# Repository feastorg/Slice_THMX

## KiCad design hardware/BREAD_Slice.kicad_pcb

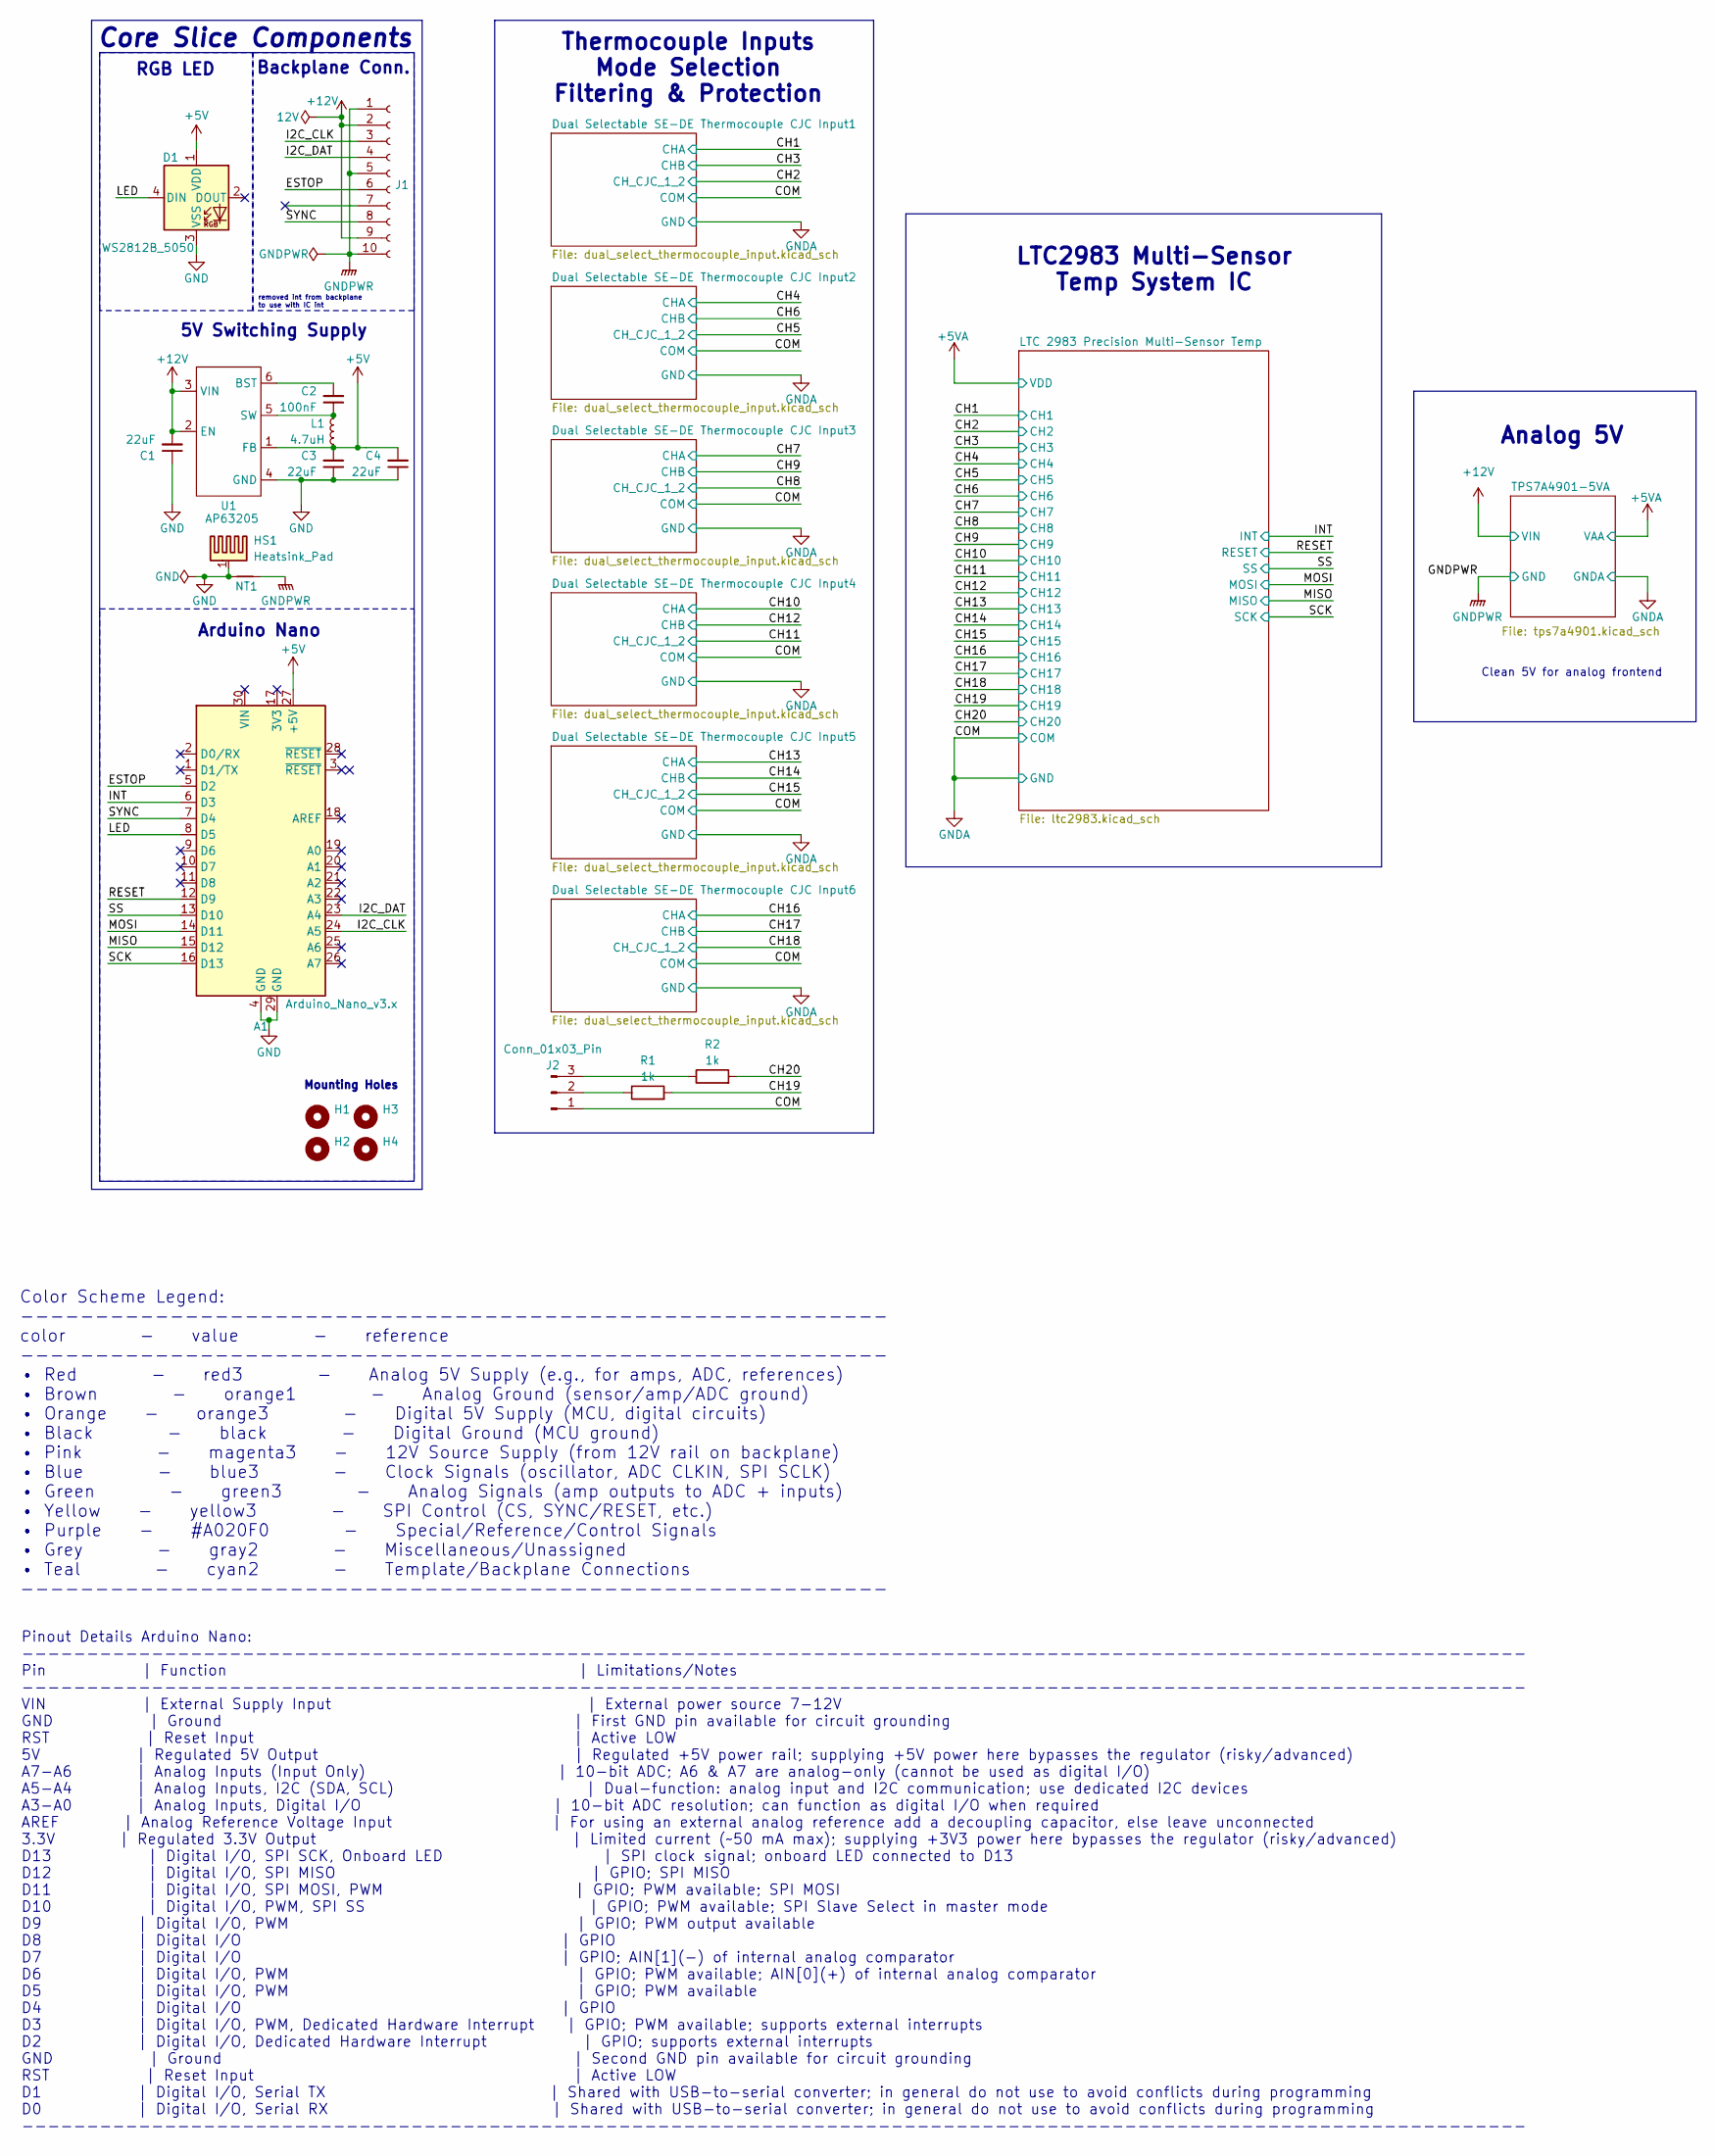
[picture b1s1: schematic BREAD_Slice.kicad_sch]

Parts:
A1: Arduino_Nano_v3.x; Arduino_Nano
C1, C3, C4: 22uF; C_1206_3216Metric
C2: 100nF; C_1206_3216Metric
D1: WS2812B_5050; WS2812-5050-4PIN
H1, H2, H3, H4: MountingHole; MountingHole_5mm
HS1: Heatsink_Pad; Thermal_Pad
J1: Conn_01x10_Female; PinSocket_1x10_P2.54mm_Horizontal
J2: Conn_01x03_Pin; PinHeader_1x03_P2.54mm_Vertical
L1: 4.7uH; L_1210_3225Metric
NT1: NetTie_2; NetTie-2_SMD_Pad2.0mm
R1, R2: 1k; R_0603_1608Metric_Pad0.98x0.95mm_HandSolder
U1: AP63205; TSOT-23-6

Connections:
+5V: A1.27 (+5V), C3.2, C4.2, D1.1 (VDD), L1.2, U1.1 (FB)
+12V: C1.2, J1.2, J1.9, U1.2 (EN), U1.3 (VIN); also elsewhere on the board
/CH19: R1.2; also elsewhere on the board
/CH20: R2.2; also elsewhere on the board
/ESTOP: A1.5 (D2), J1.6
/I2C_CLK: A1.24 (A5), J1.3
/I2C_DAT: A1.23 (A4), J1.4
/INT: A1.6 (D3); also elsewhere on the board
/LED: A1.8 (D5), D1.4 (DIN)
/MISO: A1.15 (D12); also elsewhere on the board
/MOSI: A1.14 (D11); also elsewhere on the board
/RESET: A1.12 (D9); also elsewhere on the board
/SCK: A1.16 (D13); also elsewhere on the board
/SS: A1.13 (D10); also elsewhere on the board
/SYNC: A1.7 (D4), J1.8
GND: A1.4 (GND), A1.29 (GND), C1.1, C3.1, C4.1, D1.3 (VSS), HS1.1, NT1.1, U1.4 (GND)
GNDA: J2.1; also elsewhere on the board
GNDPWR: J1.1, J1.5, J1.10, NT1.2; also elsewhere on the board
unnamed: J2.2, R1.1
unnamed: J2.3, R2.1
unnamed: C2.2, U1.6 (BST)
unnamed: C2.1, L1.1, U1.5 (SW)

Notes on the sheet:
Clean 5V for analog frontend
removed int from backplane to use with IC int
5V Switching Supply
Analog 5V
Thermocouple Inputs Mode Selection Filtering & Protection
Pinout Details Arduino Nano: -------------------------------------------------------------------------------------------------------------------- Pin | Function | Limitations/Notes -------------------------------------------------------------------------------------------------------------------- V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
RGB LED
Color Scheme Legend: ---------------------------------------------------------- color - value - reference ---------------------------------------------------------- • Red - red3 - Analog 5V Supply (e.g., for amps, ADC, references) • Brown - orange1 - Analog Ground (sensor/amp/ADC ground) • Orange -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
LTC2983 Multi-Sensor Temp System IC
Core Slice Components
Arduino Nano
Mounting Holes
Backplane Conn.

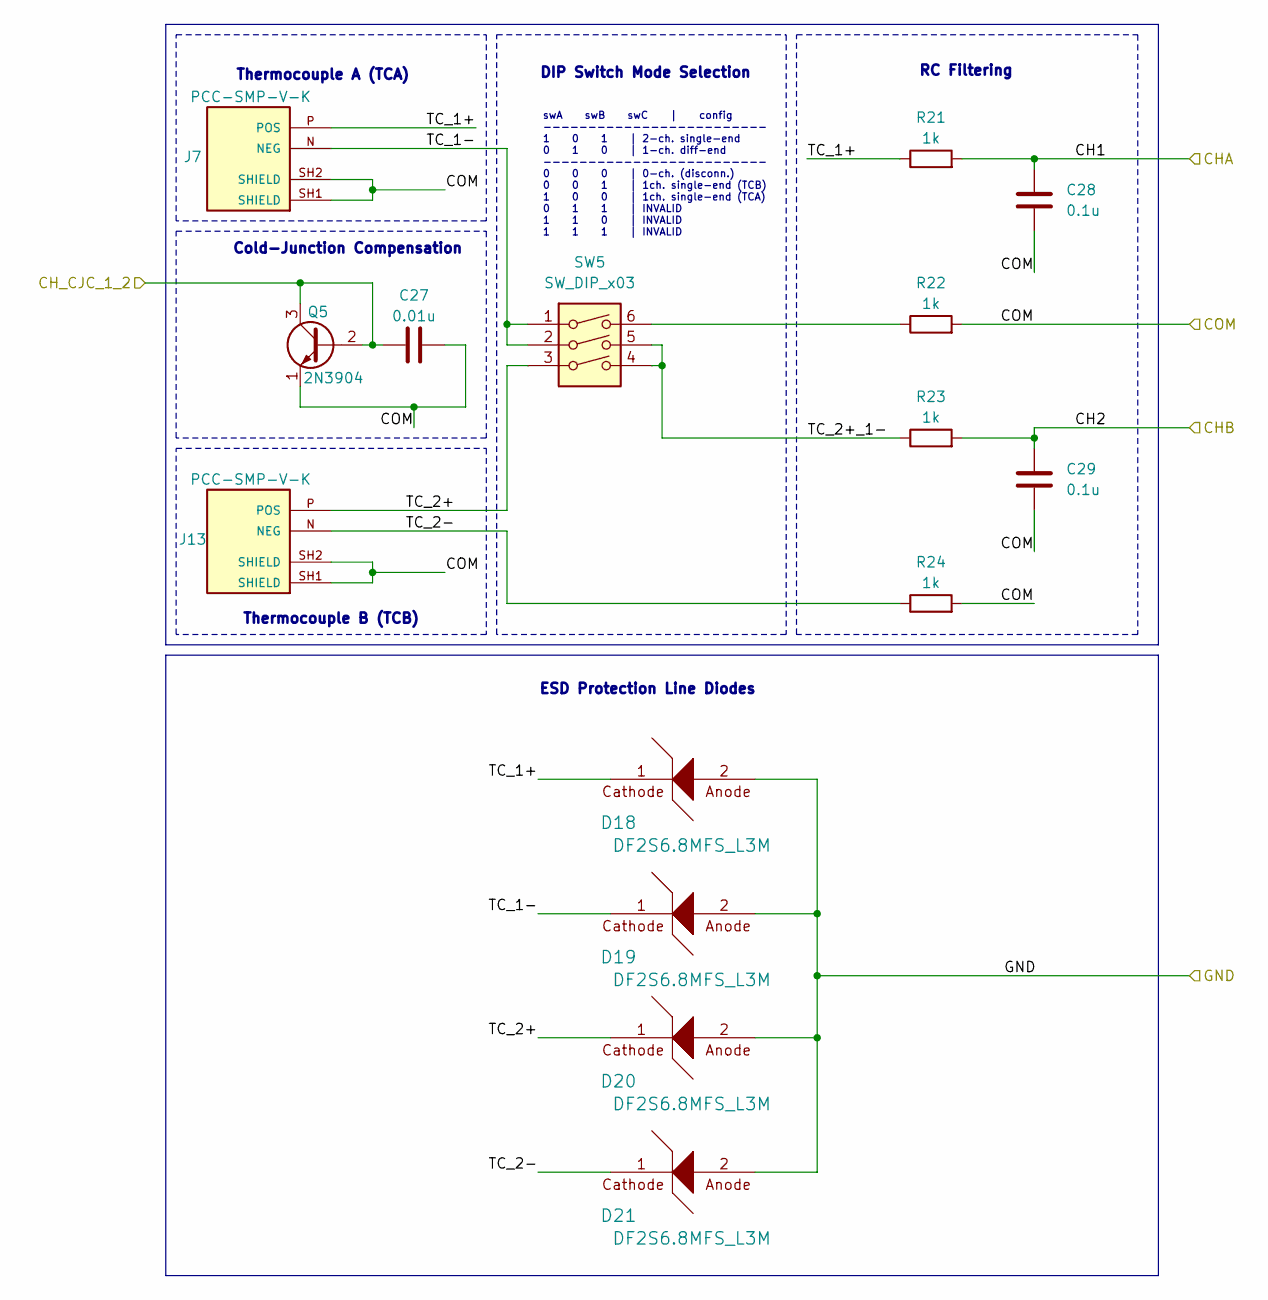
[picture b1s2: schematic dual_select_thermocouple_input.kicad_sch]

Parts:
C27: 0.01u; C_0603_1608Metric_Pad1.08x0.95mm_HandSolder
C28, C29: 0.1u; C_0603_1608Metric_Pad1.08x0.95mm_HandSolder
D18, D19, D20, D21: DF2S6.8MFS_L3M; D_SOD-923
J7, J13: PCC-SMP-V-K; OMEGA_PCC-SMP-V-K
Q5: 2N3904; TO-92_Inline
R21, R22, R23, R24: 1k; R_0603_1608Metric_Pad0.98x0.95mm_HandSolder
SW5: SW_DIP_x03; SW_DIP_SPSTx03_Slide_9.78x9.8mm_W8.61mm_P2.54mm

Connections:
/CH13: C28.1, R21.2; also elsewhere on the board
/CH14: C29.1, R23.2; also elsewhere on the board
/CH15: C27.1, Q5.2 (B), Q5.3 (C); also elsewhere on the board
/Dual Selectable SE-DE Thermocouple CJC Input5/TC_1+: D18.1, J7.P (POS), R21.1
/Dual Selectable SE-DE Thermocouple CJC Input5/TC_1-: D19.1, J7.N (NEG), SW5.1, SW5.2
/Dual Selectable SE-DE Thermocouple CJC Input5/TC_2+: D20.1, J13.P (POS), SW5.3
/Dual Selectable SE-DE Thermocouple CJC Input5/TC_2+_1-: R23.1, SW5.4, SW5.5
/Dual Selectable SE-DE Thermocouple CJC Input5/TC_2-: D21.1, J13.N (NEG), R24.1
GNDA: C27.2, C28.2, C29.2, D18.2, D19.2, D20.2, D21.2, J7.SH1 (SHIELD), J7.SH2 (SHIELD), J13.SH1 (SHIELD), J13.SH2 (SHIELD), Q5.1 (E), R22.2, R24.2; also elsewhere on the board
unnamed: R22.1, SW5.6

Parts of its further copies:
C5, C18, C21, C24, C30: 0.01u; C_0603_1608Metric_Pad1.08x0.95mm_HandSolder
C6, C7, C19, C20, C22, C23, C25, C26, C31, C32: 0.1u; C_0603_1608Metric_Pad1.08x0.95mm_HandSolder
D2, D3, D4, D5, D6, D7, D8, D9, D10, D11, D12, D13, D14, D15, D16, D17, D22, D23, D24, D25: DF2S6.8MFS_L3M; D_SOD-923
J3, J4, J5, J6, J8, J9, J10, J11, J12, J14: PCC-SMP-V-K; OMEGA_PCC-SMP-V-K
Q1, Q2, Q3, Q4, Q6: 2N3904; TO-92_Inline
R3, R4, R5, R6, R9, R10, R11, R12, R13, R14, R15, R16, R17, R18, R19, R20, R25, R26, R27, R28: 1k; R_0603_1608Metric_Pad0.98x0.95mm_HandSolder
SW1, SW2, SW3, SW4, SW6: SW_DIP_x03; SW_DIP_SPSTx03_Slide_9.78x9.8mm_W8.61mm_P2.54mm

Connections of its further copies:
/CH1: C6.1, R3.2; also elsewhere on the board
/CH2: C5.1, Q1.2 (B), Q1.3 (C); also elsewhere on the board
/CH3: C7.1, R5.2; also elsewhere on the board
/CH4: C19.1, R9.2; also elsewhere on the board
/CH5: C18.1, Q2.2 (B), Q2.3 (C); also elsewhere on the board
/CH6: C20.1, R11.2; also elsewhere on the board
/CH7: C22.1, R13.2; also elsewhere on the board
/CH8: C21.1, Q3.2 (B), Q3.3 (C); also elsewhere on the board
/CH9: C23.1, R15.2; also elsewhere on the board
/CH10: C25.1, R17.2; also elsewhere on the board
/CH11: C24.1, Q4.2 (B), Q4.3 (C); also elsewhere on the board
/CH12: C26.1, R19.2; also elsewhere on the board
/CH16: C31.1, R25.2; also elsewhere on the board
/CH17: C32.1, R27.2; also elsewhere on the board
/CH18: C30.1, Q6.2 (B), Q6.3 (C); also elsewhere on the board
/Dual Selectable SE-DE Thermocouple CJC Input1/TC_1+: D2.1, J3.P (POS), R3.1
/Dual Selectable SE-DE Thermocouple CJC Input1/TC_1-: D3.1, J3.N (NEG), SW1.1, SW1.2
/Dual Selectable SE-DE Thermocouple CJC Input1/TC_2+: D4.1, J9.P (POS), SW1.3
/Dual Selectable SE-DE Thermocouple CJC Input1/TC_2+_1-: R5.1, SW1.4, SW1.5
/Dual Selectable SE-DE Thermocouple CJC Input1/TC_2-: D5.1, J9.N (NEG), R6.1
/Dual Selectable SE-DE Thermocouple CJC Input2/TC_1+: D6.1, J4.P (POS), R9.1
/Dual Selectable SE-DE Thermocouple CJC Input2/TC_1-: D7.1, J4.N (NEG), SW2.1, SW2.2
/Dual Selectable SE-DE Thermocouple CJC Input2/TC_2+: D8.1, J10.P (POS), SW2.3
/Dual Selectable SE-DE Thermocouple CJC Input2/TC_2+_1-: R11.1, SW2.4, SW2.5
/Dual Selectable SE-DE Thermocouple CJC Input2/TC_2-: D9.1, J10.N (NEG), R12.1
/Dual Selectable SE-DE Thermocouple CJC Input3/TC_1+: D10.1, J5.P (POS), R13.1
/Dual Selectable SE-DE Thermocouple CJC Input3/TC_1-: D11.1, J5.N (NEG), SW3.1, SW3.2
/Dual Selectable SE-DE Thermocouple CJC Input3/TC_2+: D12.1, J11.P (POS), SW3.3
/Dual Selectable SE-DE Thermocouple CJC Input3/TC_2+_1-: R15.1, SW3.4, SW3.5
/Dual Selectable SE-DE Thermocouple CJC Input3/TC_2-: D13.1, J11.N (NEG), R16.1
/Dual Selectable SE-DE Thermocouple CJC Input4/TC_1+: D14.1, J6.P (POS), R17.1
/Dual Selectable SE-DE Thermocouple CJC Input4/TC_1-: D15.1, J6.N (NEG), SW4.1, SW4.2
/Dual Selectable SE-DE Thermocouple CJC Input4/TC_2+: D16.1, J12.P (POS), SW4.3
/Dual Selectable SE-DE Thermocouple CJC Input4/TC_2+_1-: R19.1, SW4.4, SW4.5
/Dual Selectable SE-DE Thermocouple CJC Input4/TC_2-: D17.1, J12.N (NEG), R20.1
/Dual Selectable SE-DE Thermocouple CJC Input6/TC_1+: D22.1, J8.P (POS), R25.1
/Dual Selectable SE-DE Thermocouple CJC Input6/TC_1-: D23.1, J8.N (NEG), SW6.1, SW6.2
/Dual Selectable SE-DE Thermocouple CJC Input6/TC_2+: D24.1, J14.P (POS), SW6.3
/Dual Selectable SE-DE Thermocouple CJC Input6/TC_2+_1-: R27.1, SW6.4, SW6.5
/Dual Selectable SE-DE Thermocouple CJC Input6/TC_2-: D25.1, J14.N (NEG), R28.1
GNDA: C5.2, C6.2, C7.2, C18.2, C19.2, C20.2, C21.2, C22.2, C23.2, C24.2, C25.2, C26.2, C30.2, C31.2, C32.2, D2.2, D3.2, D4.2, D5.2, D6.2, D7.2, D8.2, D9.2, D10.2, D11.2, D12.2, D13.2, D14.2, D15.2, D16.2, D17.2, D22.2, D23.2, D24.2, D25.2, J3.SH1 (SHIELD), J3.SH2 (SHIELD), J4.SH1 (SHIELD), J4.SH2 (SHIELD), J5.SH1 (SHIELD), J5.SH2 (SHIELD), J6.SH1 (SHIELD), J6.SH2 (SHIELD), J8.SH1 (SHIELD), J8.SH2 (SHIELD), J9.SH1 (SHIELD), J9.SH2 (SHIELD), J10.SH1 (SHIELD), J10.SH2 (SHIELD), J11.SH1 (SHIELD), J11.SH2 (SHIELD), J12.SH1 (SHIELD), J12.SH2 (SHIELD), J14.SH1 (SHIELD), J14.SH2 (SHIELD), Q1.1 (E), Q2.1 (E), Q3.1 (E), Q4.1 (E), Q6.1 (E), R4.2, R6.2, R10.2, R12.2, R14.2, R16.2, R18.2, R20.2, R26.2, R28.2; also elsewhere on the board
unnamed: R4.1, SW1.6
unnamed: R10.1, SW2.6
unnamed: R14.1, SW3.6
unnamed: R18.1, SW4.6
unnamed: R26.1, SW6.6

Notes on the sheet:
Thermocouple A (TCA)
RC Filtering
ESD Protection Line Diodes
Cold-Junction Compensation
swA swB swC | config ------------------------- 1 0 1 | 2-ch. single-end 0 1 0 | 1-ch. diff-end ------------------------- 0 0 0 | 0-ch. (disconn.) 0 0 1 | 1ch. single-end (TCB) 1 0 0 | 1ch. single-end (TCA) 0 1 1 | INVALID 1 1 0 | INVALID 1 1 1 | INVALID
DIP Switch Mode Selection
Thermocouple B (TCB)

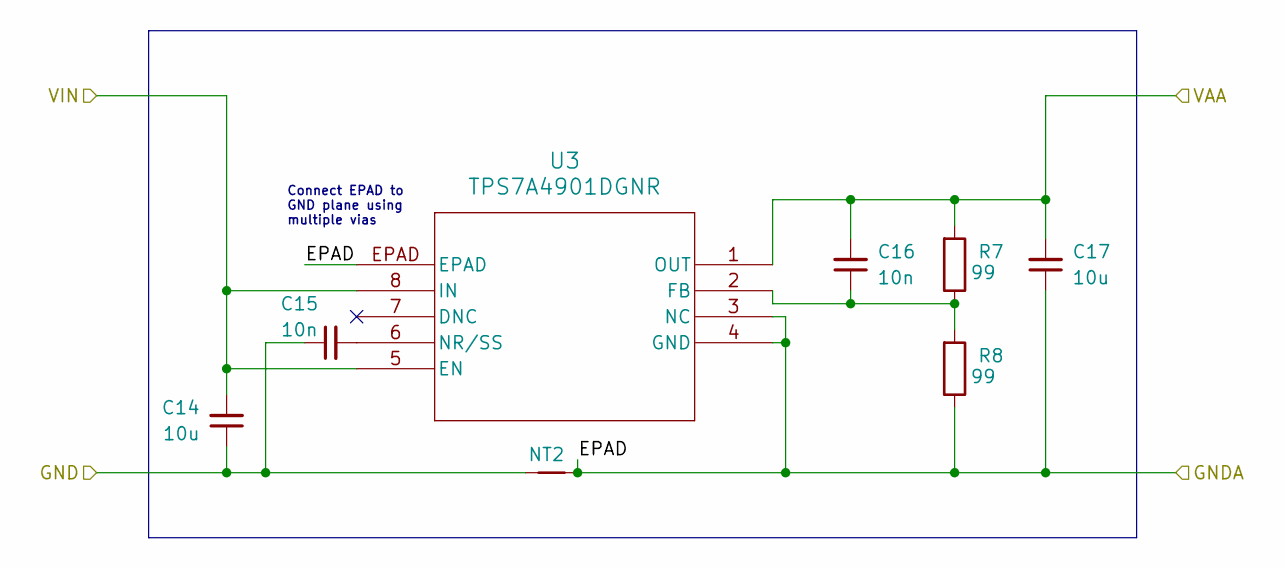
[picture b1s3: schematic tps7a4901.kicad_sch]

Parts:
C14, C17: 10u; C_0805_2012Metric_Pad1.18x1.45mm_HandSolder
C15, C16: 10n; C_0805_2012Metric_Pad1.18x1.45mm_HandSolder
NT2: NetTie_2; NetTie-2_SMD_Pad2.0mm
R7, R8: 99; R_0805_2012Metric_Pad1.20x1.40mm_HandSolder
U3: TPS7A4901DGNR; DGN8_1P89X1P57

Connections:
+5VA: C16.2, C17.2, R7.2, U3.1 (OUT); also elsewhere on the board
+12V: C14.2, U3.5 (EN), U3.8 (IN); also elsewhere on the board
GNDA: C17.1, NT2.2, R8.1, U3.3 (NC), U3.4 (GND), U3.EPAD; also elsewhere on the board
GNDPWR: C14.1, C15.1, NT2.1; also elsewhere on the board
unnamed: C16.1, R7.1, R8.2, U3.2 (FB)
unnamed: C15.2, U3.6 (NR/SS)

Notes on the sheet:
Connect EPAD to GND plane using multiple vias

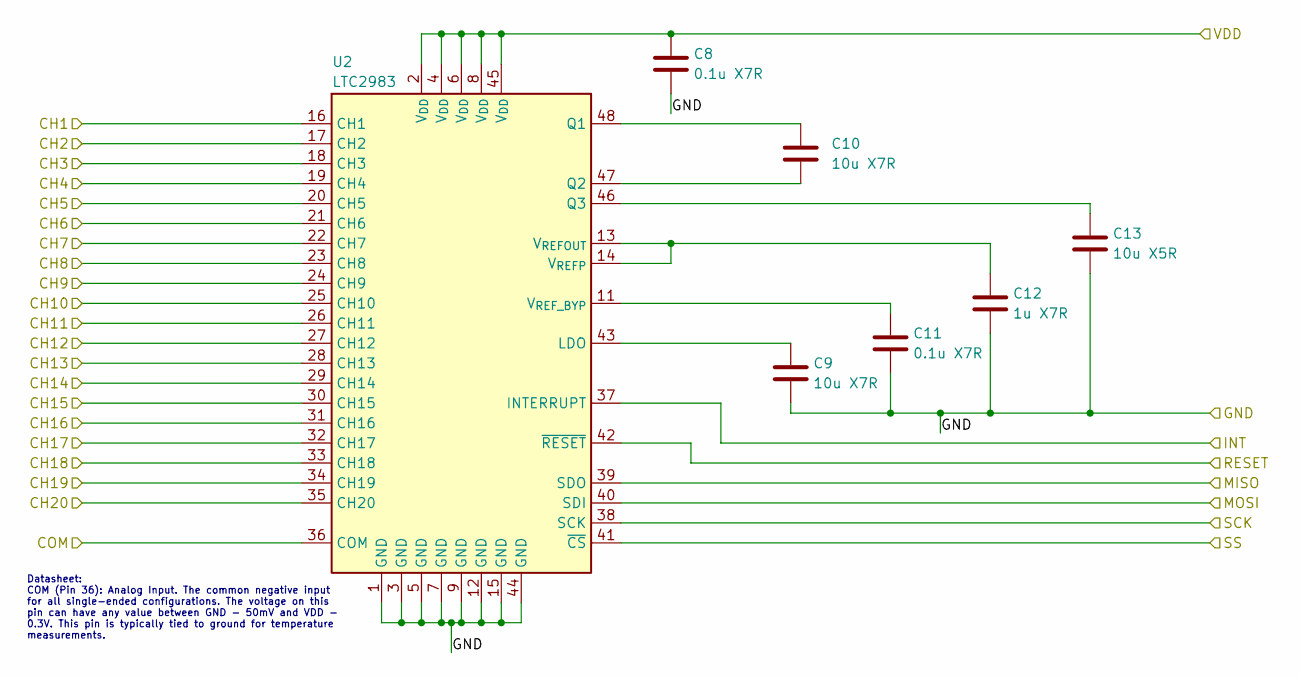
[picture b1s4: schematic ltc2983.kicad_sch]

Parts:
C8: 0.1u X7R; C_0603_1608Metric_Pad1.08x0.95mm_HandSolder
C9, C10: 10u X7R; C_1206_3216Metric_Pad1.33x1.80mm_HandSolder
C11: 0.1u X7R; C_1206_3216Metric_Pad1.33x1.80mm_HandSolder
C12: 1u X7R; C_1206_3216Metric_Pad1.33x1.80mm_HandSolder
C13: 10u X5R; C_1206_3216Metric_Pad1.33x1.80mm_HandSolder
U2: LTC2983; LQFP-48_7x7mm_P0.5mm

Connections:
+5VA: C8.1, U2.2 (V_{DD}), U2.4 (V_{DD}), U2.6 (V_{DD}), U2.8 (V_{DD}), U2.45 (V_{DD}); also elsewhere on the board
/CH1: U2.16 (CH1); also elsewhere on the board
/CH2: U2.17 (CH2); also elsewhere on the board
/CH3: U2.18 (CH3); also elsewhere on the board
/CH4: U2.19 (CH4); also elsewhere on the board
/CH5: U2.20 (CH5); also elsewhere on the board
/CH6: U2.21 (CH6); also elsewhere on the board
/CH7: U2.22 (CH7); also elsewhere on the board
/CH8: U2.23 (CH8); also elsewhere on the board
/CH9: U2.24 (CH9); also elsewhere on the board
/CH10: U2.25 (CH10); also elsewhere on the board
/CH11: U2.26 (CH11); also elsewhere on the board
/CH12: U2.27 (CH12); also elsewhere on the board
/CH13: U2.28 (CH13); also elsewhere on the board
/CH14: U2.29 (CH14); also elsewhere on the board
/CH15: U2.30 (CH15); also elsewhere on the board
/CH16: U2.31 (CH16); also elsewhere on the board
/CH17: U2.32 (CH17); also elsewhere on the board
/CH18: U2.33 (CH18); also elsewhere on the board
/CH19: U2.34 (CH19); also elsewhere on the board
/CH20: U2.35 (CH20); also elsewhere on the board
/INT: U2.37 (INTERRUPT); also elsewhere on the board
/MISO: U2.39 (SDO); also elsewhere on the board
/MOSI: U2.40 (SDI); also elsewhere on the board
/RESET: U2.42 (~RESET); also elsewhere on the board
/SCK: U2.38 (SCK); also elsewhere on the board
/SS: U2.41 (~CS); also elsewhere on the board
GNDA: C8.2, C9.2, C11.2, C12.2, C13.2, U2.1 (GND), U2.3 (GND), U2.5 (GND), U2.7 (GND), U2.9 (GND), U2.12 (GND), U2.15 (GND), U2.36 (COM), U2.44 (GND); also elsewhere on the board
unnamed: C9.1, U2.43 (LDO)
unnamed: C10.1, U2.48 (Q1)
unnamed: C10.2, U2.47 (Q2)
unnamed: C13.1, U2.46 (Q3)
unnamed: C12.1, U2.13 (V_{REFOUT}), U2.14 (V_{REFP})
unnamed: C11.1, U2.11 (V_{REF_BYP})

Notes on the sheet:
Datasheet: COM (Pin 36): Analog Input. The common negative input for all single-ended configurations. The voltage on this pin can have any value between GND - 50mV and VDD - 0.3V. This pin is typically tied to ground for temperature measurements.

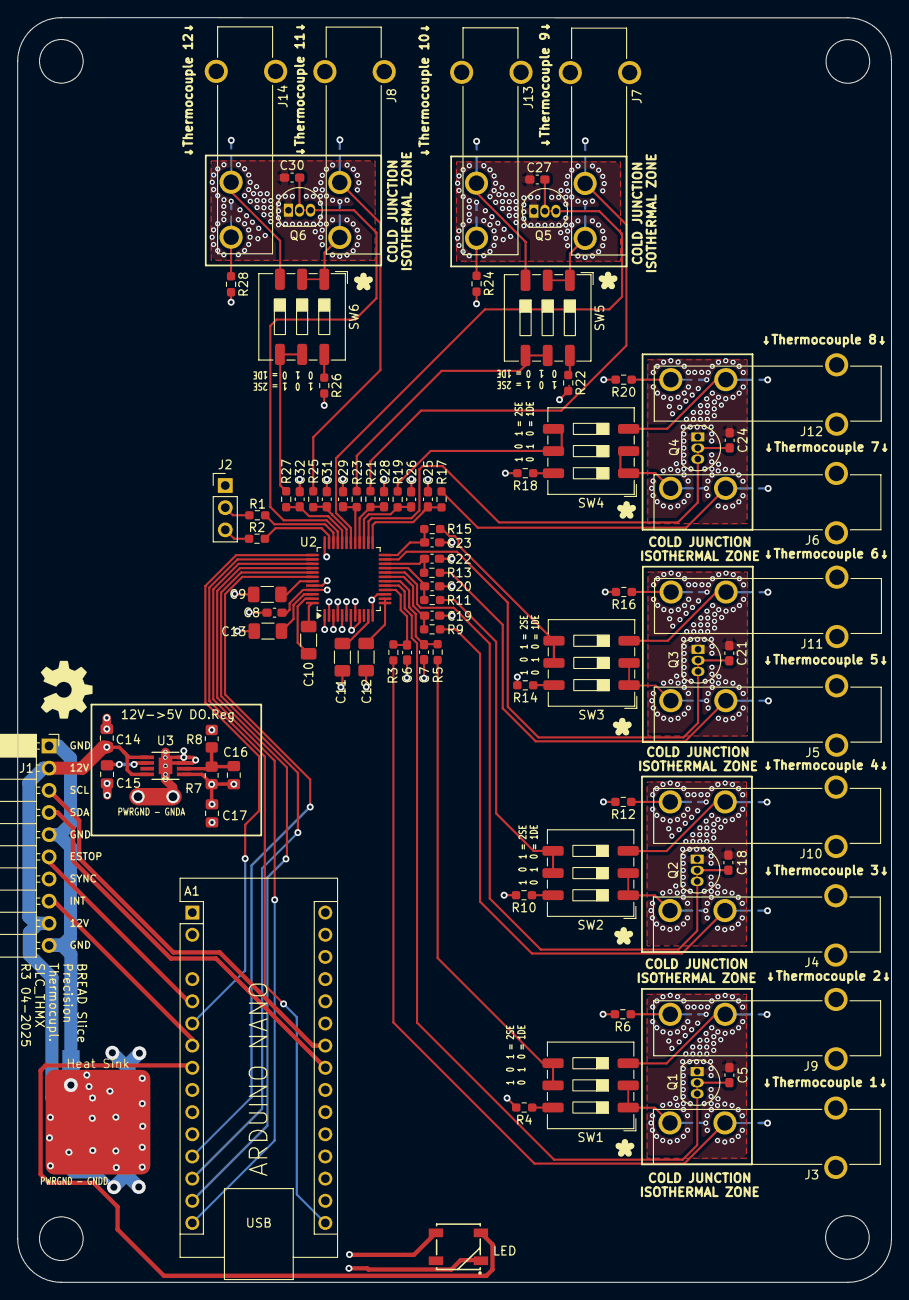
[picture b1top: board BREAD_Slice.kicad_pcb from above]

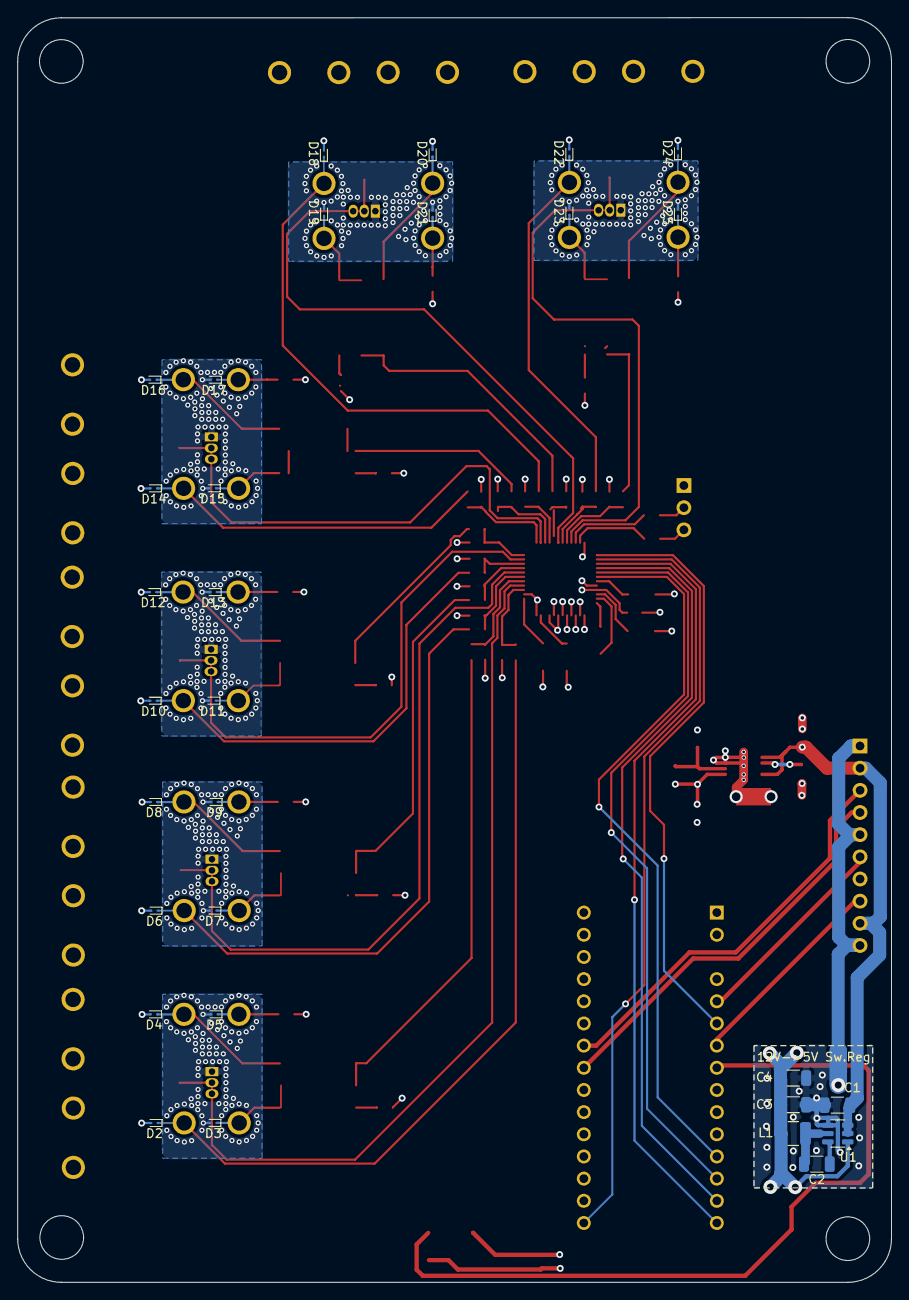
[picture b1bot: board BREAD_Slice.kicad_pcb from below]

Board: 4 copper layers, 100.1 x 144.9 mm, 124 parts (31 on the bottom side), 85 nets.

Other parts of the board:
Logo1: Logo_Open_Hardware_Small; OSHW-Symbol_6.7x6mm_SilkScreen

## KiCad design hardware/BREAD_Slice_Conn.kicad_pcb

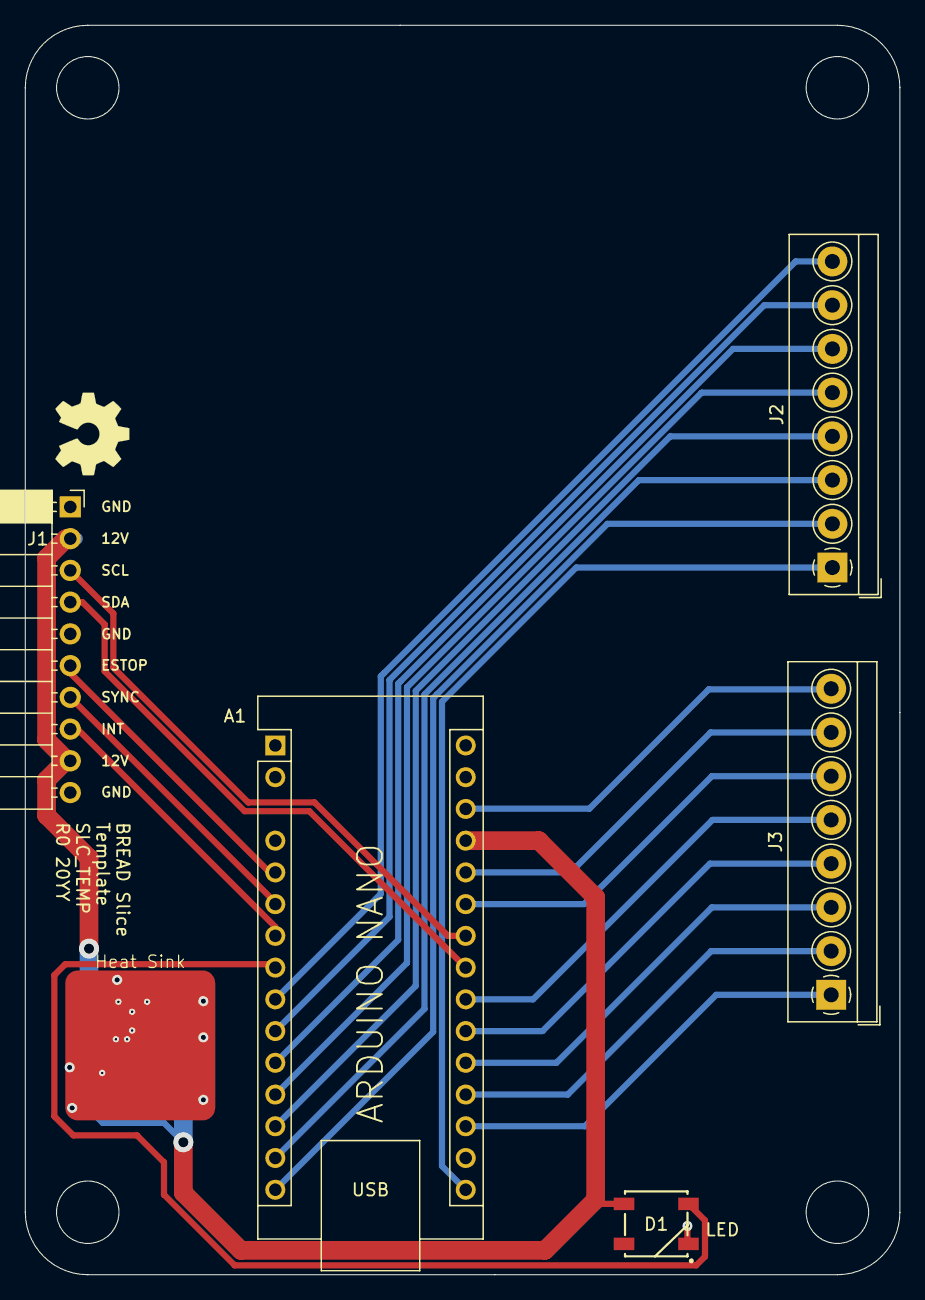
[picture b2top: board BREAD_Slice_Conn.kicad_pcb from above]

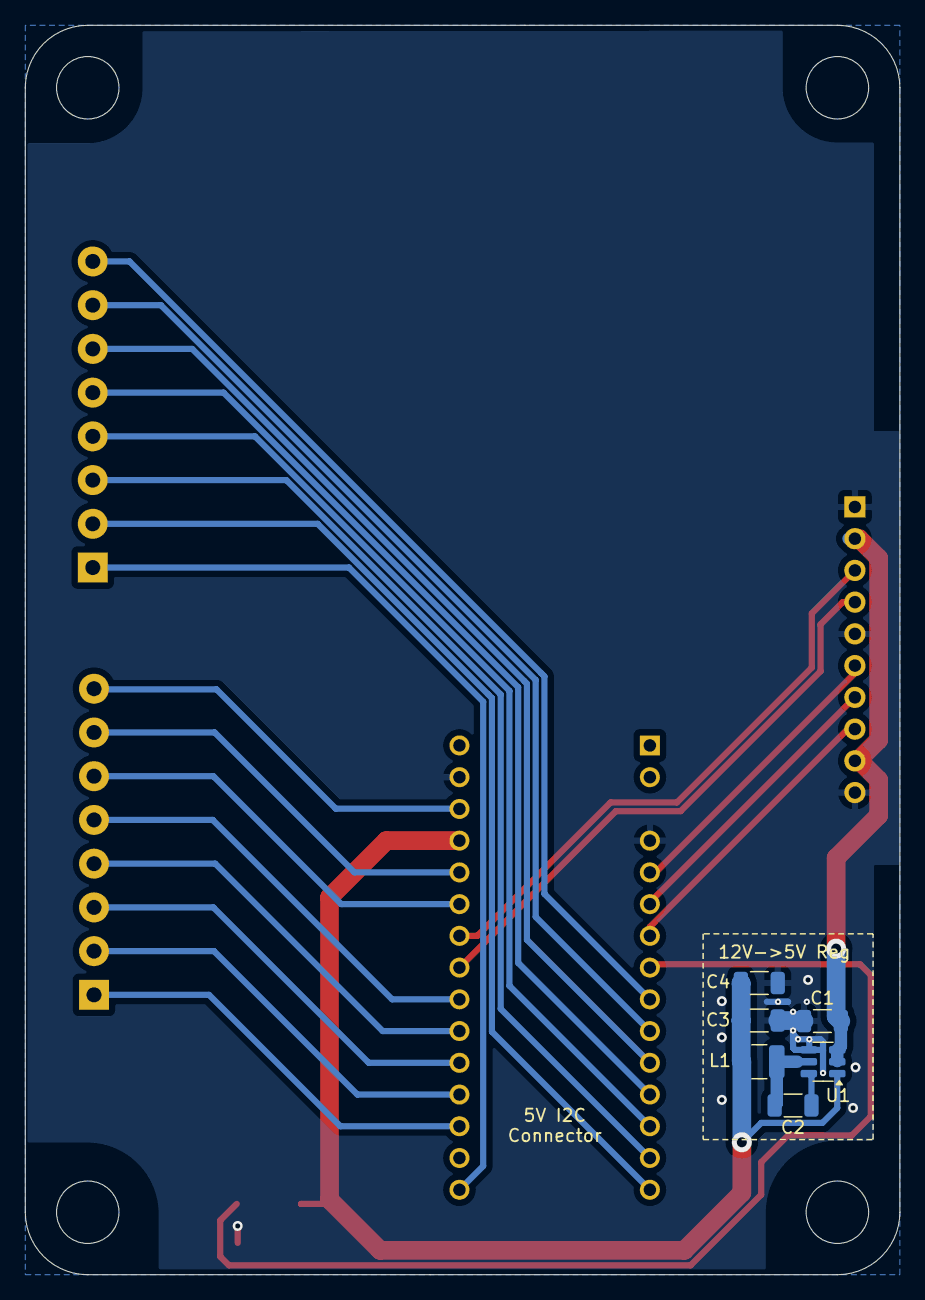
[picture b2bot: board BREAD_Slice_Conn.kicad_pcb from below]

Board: 2 copper layers, 70.0 x 100.0 mm, 17 parts (6 on the bottom side), 27 nets.

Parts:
A1: Arduino_Nano_v3.x; Arduino_Nano
C1, C3, C4: 22uF; C_1206_3216Metric
C2: 100nF; C_1206_3216Metric
D1: WS2812B_5050; WS2812-5050-4PIN
H1, H2, H3, H4: MountingHole; MountingHole_5mm
HS1: Heatsink_Pad; Thermal Pad
J1: Conn_01x10_Female; PinSocket_1x10_P2.54mm_Horizontal
J2, J3: Conn_01x08; TerminalBlock_4Ucon_1x08_P3.50mm_Horizontal
L1: 4.7uH; L_1210_3225Metric
Logo1: Logo_Open_Hardware_Small; OSHW-Symbol_6.7x6mm_SilkScreen
U1: TSOT-23-6

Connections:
+5V: A1.27 (+5V), C3.2, C4.2, D1.1 (VDD), L1.2, U1.1 (FB)
+12V: C1.2, J1.2, J1.9, U1.2 (EN), U1.3 (VIN)
/A0: A1.19 (A0), J3.2
/A1: A1.20 (A1), J3.3
/A2: A1.21 (A2), J3.4
/A3: A1.22 (A3), J3.5
/A6: A1.25 (A6), J3.6
/A7: A1.26 (A7), J3.7
/AREF: A1.18 (AREF), J3.1
/D6: A1.9 (D6), J2.8
/D7: A1.10 (D7), J2.7
/D8: A1.11 (D8), J2.6
/D9: A1.12 (D9), J2.5
/D10: A1.13 (D10), J2.4
/D11: A1.14 (D11), J2.3
/D12: A1.15 (D12), J2.2
/D13: A1.16 (D13), J2.1
/E_STOP: A1.5 (D2), J1.6
/I2C_CLK: A1.24 (A5), J1.3
/I2C_DAT: A1.23 (A4), J1.4
/INT: A1.6 (D3), J1.7
/LED: A1.8 (D5), D1.4 (DIN)
/RESET: A1.28 (~RESET), J3.8
/SYNC: A1.7 (D4), J1.8
GND: A1.4 (GND), A1.29 (GND), C1.1, C3.1, C4.1, D1.3 (VSS), HS1.1, J1.1, J1.5, J1.10, U1.4 (GND)
unnamed: C2.2, U1.6 (BST)
unnamed: C2.1, L1.1, U1.5 (SW)

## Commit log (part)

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2025-04-09 completed schematic and board
2025-04-19 minor tweaks
2025-05-04 update dip switches to reflect chosen part
2026-05-20 Add slice.yaml manifest (schema v1.0)
2026-05-24 Add KiBot/docs pipeline (4-layer)
2026-05-24 Update TODO with CI results
2026-05-24 Standardize TODO.md with Pass 1/Pass 2 structure
